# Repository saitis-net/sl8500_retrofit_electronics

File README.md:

# sl8500_retrofit_electronics
Kicad projects for the hardware parts

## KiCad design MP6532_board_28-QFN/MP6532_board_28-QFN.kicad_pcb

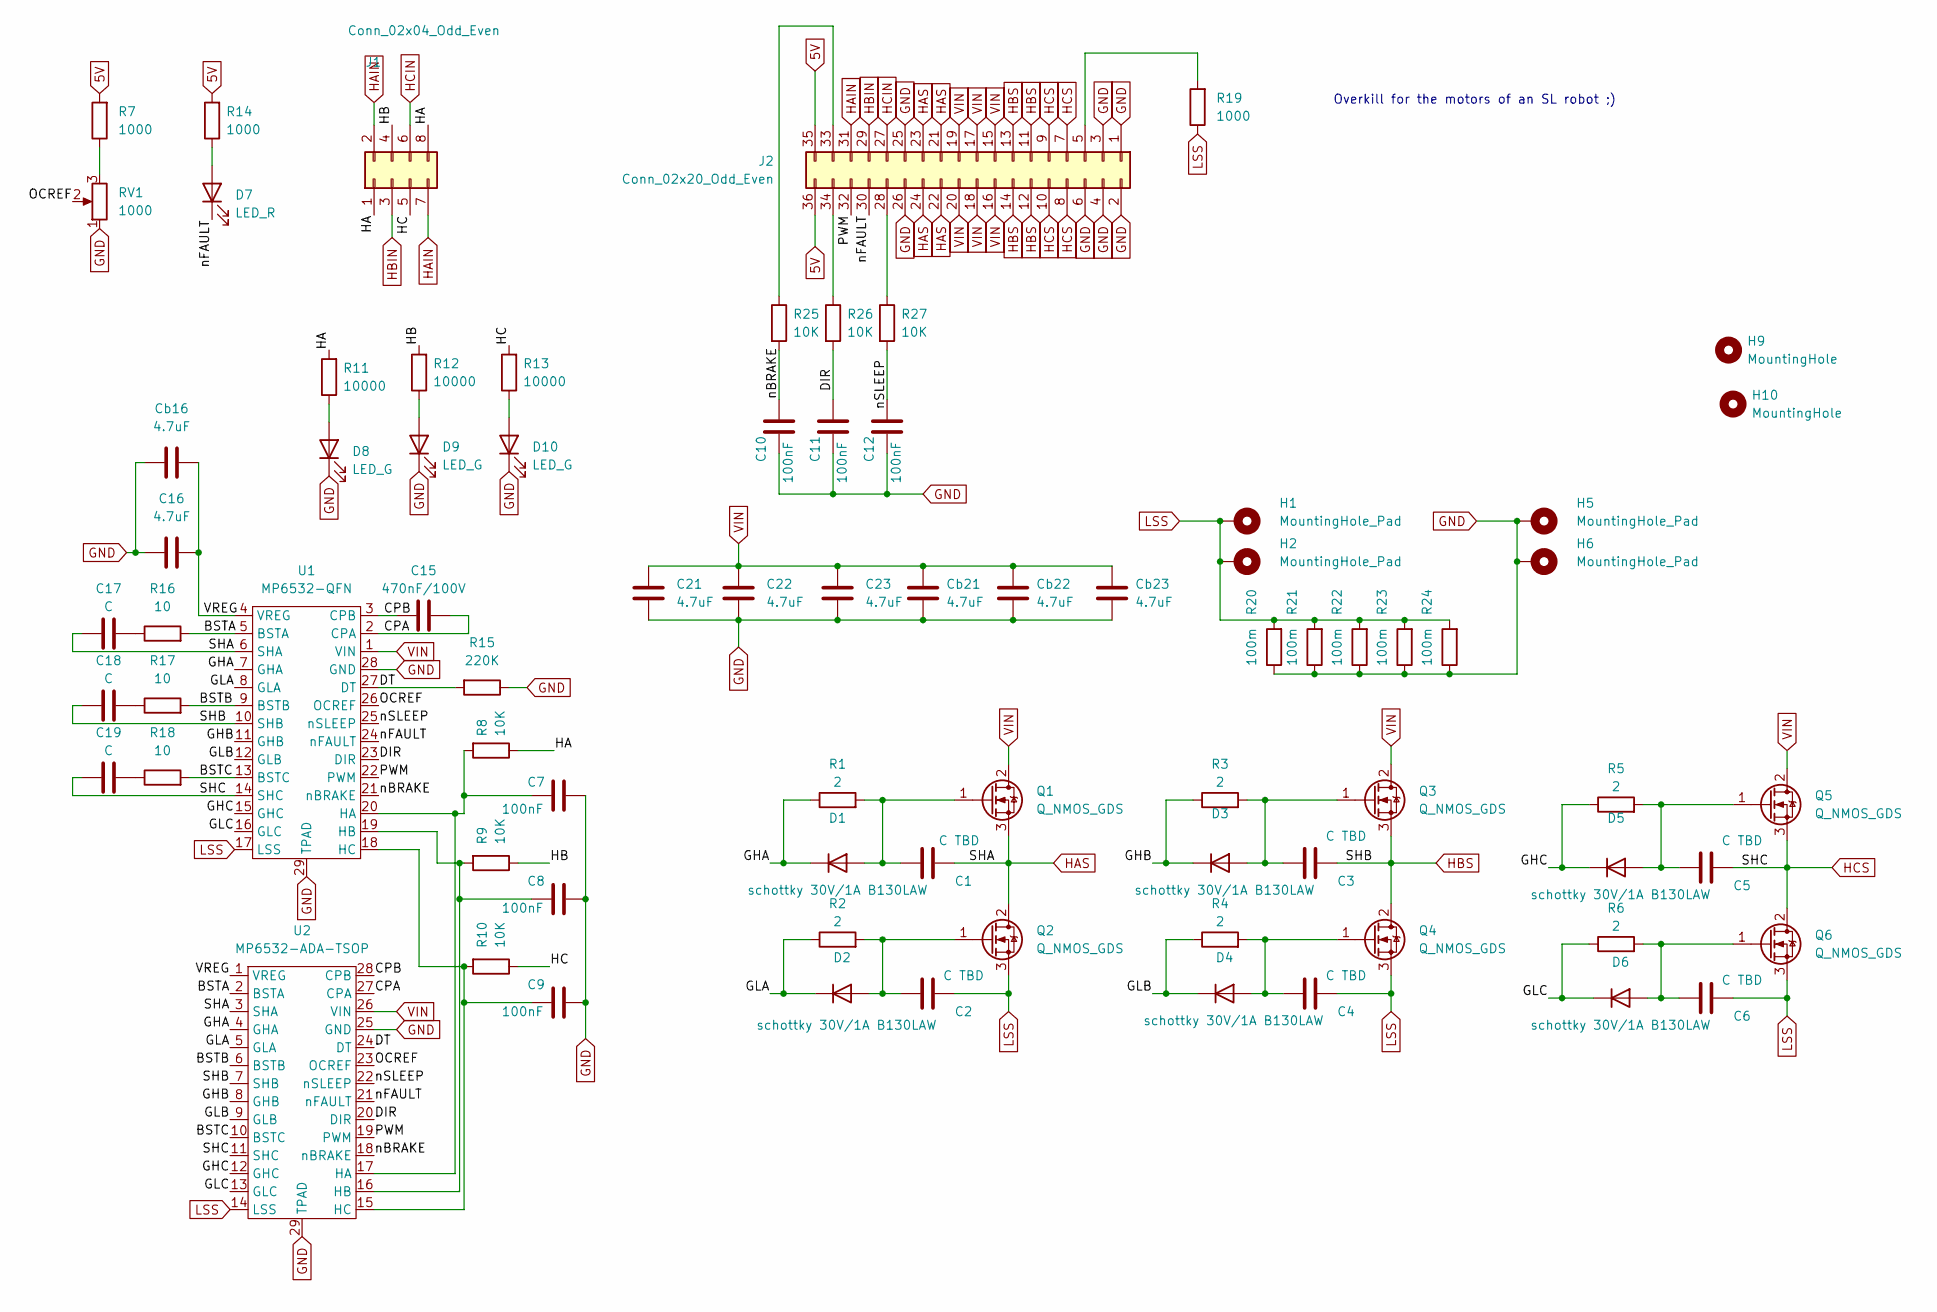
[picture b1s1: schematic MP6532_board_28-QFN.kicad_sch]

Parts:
C1, C2, C3, C4, C5, C6: C TBD; C_0603_1608Metric
C7, C8, C9, C10, C11, C12: 100nF; C_0603_1608Metric
C15: 470nF/100V; C_0805_2012Metric
C16, C21, C22, C23: 4.7uF; C_1210_3225Metric
C17, C18, C19: C; C_0603_1608Metric
Cb16, Cb21, Cb22, Cb23: 4.7uF; C_1210_3225Metric
D1, D2, D3, D4, D5, D6: schottky 30V/1A B130LAW; D_SOD-123
D7: LED_R; LED_0805_2012Metric
D8, D9, D10: LED_G; LED_0805_2012Metric
H1, H2, H5, H6: MountingHole_Pad; Pin_D1.2mm_L10.2mm_W2.9mm_FlatFork
H9, H10: MountingHole; MountingHole_3.2mm_M3_DIN965
J1: Conn_02x04_Odd_Even; PinHeader_2x04_P2.54mm_Horizontal
J2: Conn_02x20_Odd_Even; PinHeader_2x18_P2.54mm_Horizontal
Q1, Q2, Q3, Q4, Q5, Q6: Q_NMOS_GDS; TO-252-2
R1, R2, R3, R4, R5, R6: 2; R_1210_3225Metric
R7, R14, R19: 1000; R_0603_1608Metric
R8, R9, R10, R25, R26, R27: 10K; R_0603_1608Metric
R11, R12, R13: 10000; R_0603_1608Metric
R15: 220K; R_0603_1608Metric
R16, R17, R18: 10; R_0603_1608Metric
R20, R21, R22, R23, R24: 100m; R_1206_3216Metric
RV1: 1000; Potentiometer_Bourns_3296P_Horizontal
U1: MP6532-QFN; QFN-28-1EP_4x4mm_P0.4mm_EP2.6x2.6mm_ThermalVias
U2: MP6532-ADA-TSOP; 28-pin-deca

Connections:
5V: J2.35, J2.36, R7.2, R14.2
/BSTA: R16.2, U1.5 (BSTA), U2.2 (BSTA)
/BSTB: R17.2, U1.9 (BSTB), U2.6 (BSTB)
/BSTC: R18.2, U1.13 (BSTC), U2.10 (BSTC)
/CPA: C15.2, U1.2 (CPA), U2.27 (CPA)
/CPB: C15.1, U1.3 (CPB), U2.28 (CPB)
/DIR: C11.2, R26.2, U1.23 (DIR), U2.20 (DIR)
/DT: R15.2, U1.27 (DT), U2.24 (DT)
/GHA: D1.1 (K), R1.1, U1.7 (GHA), U2.4 (GHA)
/GHB: D3.1 (K), R3.1, U1.11 (GHB), U2.8 (GHB)
/GHC: D5.1 (K), R5.1, U1.15 (GHC), U2.12 (GHC)
/GLA: D2.1 (K), R2.1, U1.8 (GLA), U2.5 (GLA)
/GLB: D4.1 (K), R4.1, U1.12 (GLB), U2.9 (GLB)
/GLC: D6.1 (K), R6.1, U1.16 (GLC), U2.13 (GLC)
/HA: J1.1, J1.8, R8.1, R11.2
/HB: J1.4, R9.1, R12.2
/HC: J1.5, R10.1, R13.2
/OCREF: RV1.2, U1.26 (OCREF), U2.23 (OCREF)
/PWM: J2.32, U1.22 (PWM), U2.19 (PWM)
/VREG: C16.1, Cb16.1, U1.4 (VREG), U2.1 (VREG)
/nBRAKE: C10.2, R25.2, U1.21 (nBRAKE), U2.18 (nBRAKE)
/nFAULT: D7.1 (K), J2.30, U1.24 (nFAULT), U2.21 (nFAULT)
/nSLEEP: C12.2, R27.2, U1.25 (nSLEEP), U2.22 (nSLEEP)
GND: C7.2, C8.2, C9.2, C10.1, C11.1, C12.1, C16.2, C21.2, C22.2, C23.2, Cb16.2, Cb21.2, Cb22.2, Cb23.2, D8.1 (K), D9.1 (K), D10.1 (K), H5.1, H6.1, J2.1, J2.2, J2.3, J2.4, J2.6, J2.25, J2.26, R15.1, R20.1, R21.1, R22.1, R23.1, R24.1, RV1.1, U1.28 (GND), U1.29 (TPAD), U2.25 (GND), U2.29 (TPAD)
HAIN: J1.2, J1.7, J2.31
HAS: C1.1, C17.1, J2.21, J2.22, J2.23, J2.24, Q1.3 (S), Q2.2 (D), U1.6 (SHA), U2.3 (SHA)
HBIN: J1.3, J2.29
HBS: C3.1, C18.1, J2.11, J2.12, J2.13, J2.14, Q3.3 (S), Q4.2 (D), U1.10 (SHB), U2.7 (SHB)
HCIN: J1.6, J2.27
HCS: C5.1, C19.1, J2.7, J2.8, J2.9, J2.10, Q5.3 (S), Q6.2 (D), U1.14 (SHC), U2.11 (SHC)
LSS: C2.1, C4.1, C6.1, H1.1, H2.1, Q2.3 (S), Q4.3 (S), Q6.3 (S), R19.1, R20.2, R21.2, R22.2, R23.2, R24.2, U1.17 (LSS), U2.14 (LSS)
unnamed: C1.2, D1.2 (A), Q1.1 (G), R1.2
unnamed: C2.2, D2.2 (A), Q2.1 (G), R2.2
unnamed: C3.2, D3.2 (A), Q3.1 (G), R3.2
unnamed: C4.2, D4.2 (A), Q4.1 (G), R4.2
unnamed: C5.2, D5.2 (A), Q5.1 (G), R5.2
unnamed: C6.2, D6.2 (A), Q6.1 (G), R6.2
unnamed: C7.1, R8.2, U1.20 (HA), U2.17 (HA)
unnamed: C8.1, R9.2, U1.19 (HB), U2.16 (HB)
unnamed: C9.1, R10.2, U1.18 (HC), U2.15 (HC)
unnamed: C17.2, R16.1
unnamed: C18.2, R17.1
unnamed: C19.2, R18.1
unnamed: D7.2 (A), R14.1
unnamed: D8.2 (A), R11.1
unnamed: D9.2 (A), R12.1
unnamed: D10.2 (A), R13.1
unnamed: J2.5, R19.2
unnamed: J2.28, R27.1
unnamed: J2.33, R25.1
unnamed: J2.34, R26.1
unnamed: R7.1, RV1.3
VIN: C21.1, C22.1, C23.1, Cb21.1, Cb22.1, Cb23.1, J2.15, J2.16, J2.17, J2.18, J2.19, J2.20, Q1.2 (D), Q3.2 (D), Q5.2 (D), U1.1 (VIN), U2.26 (VIN)

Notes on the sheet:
Overkill for the motors of an SL robot ;)

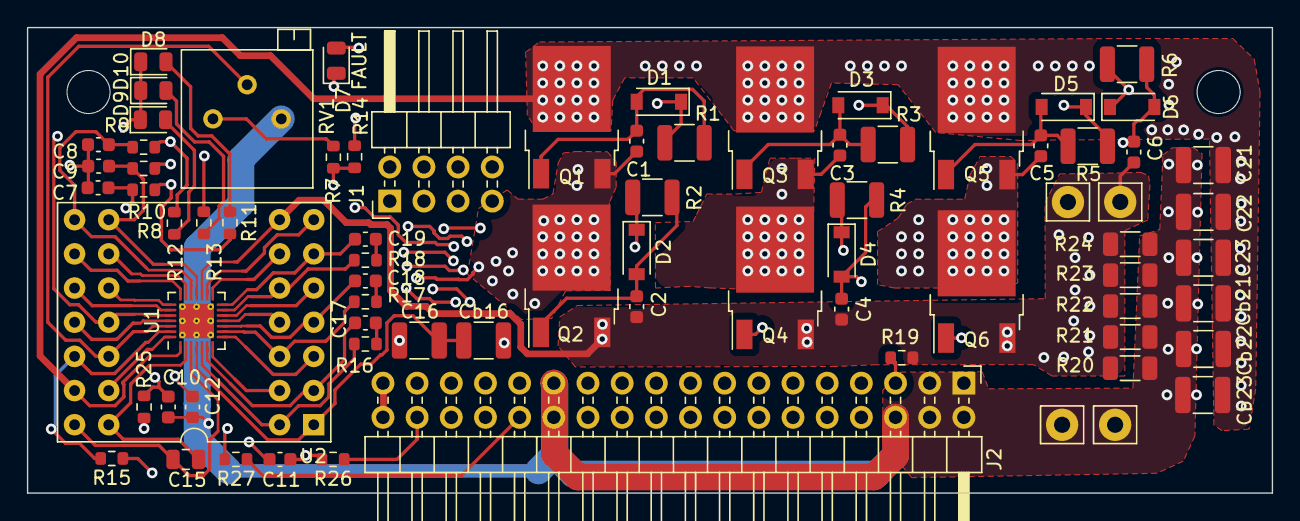
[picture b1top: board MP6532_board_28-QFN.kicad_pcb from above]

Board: 4 copper layers, 92.5 x 34.6 mm, 78 parts (0 on the bottom side), 53 nets.

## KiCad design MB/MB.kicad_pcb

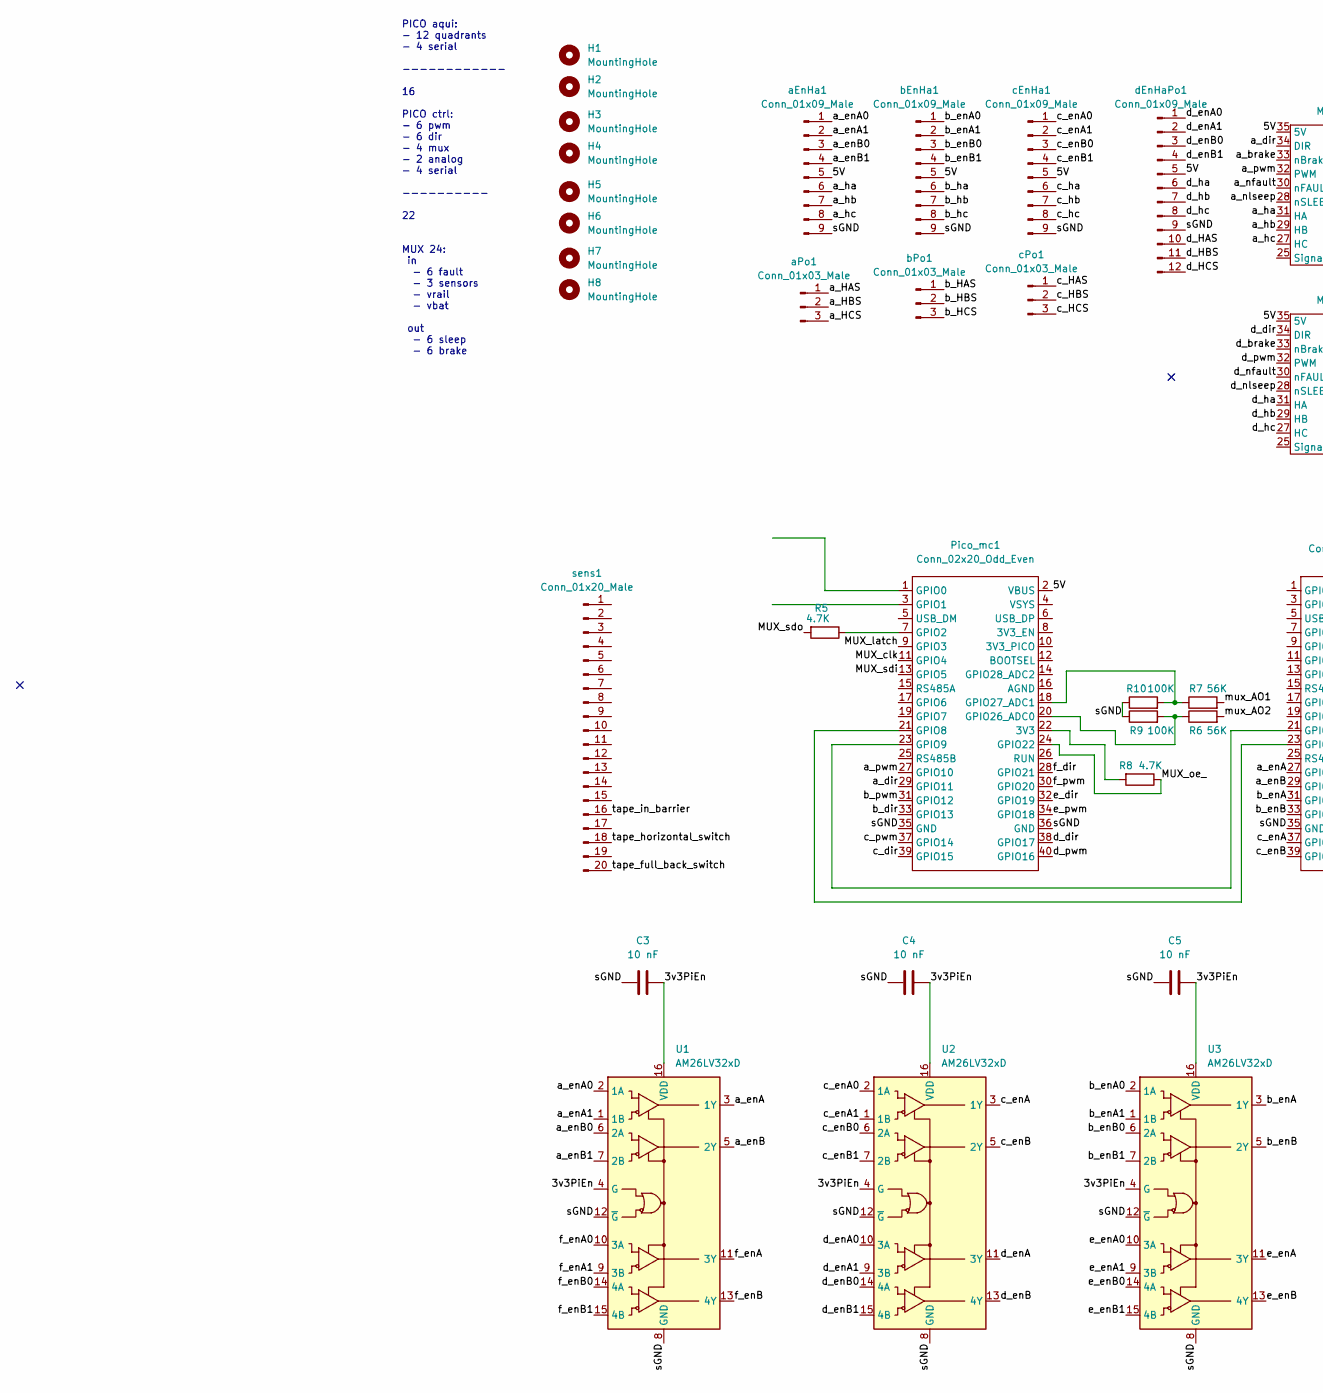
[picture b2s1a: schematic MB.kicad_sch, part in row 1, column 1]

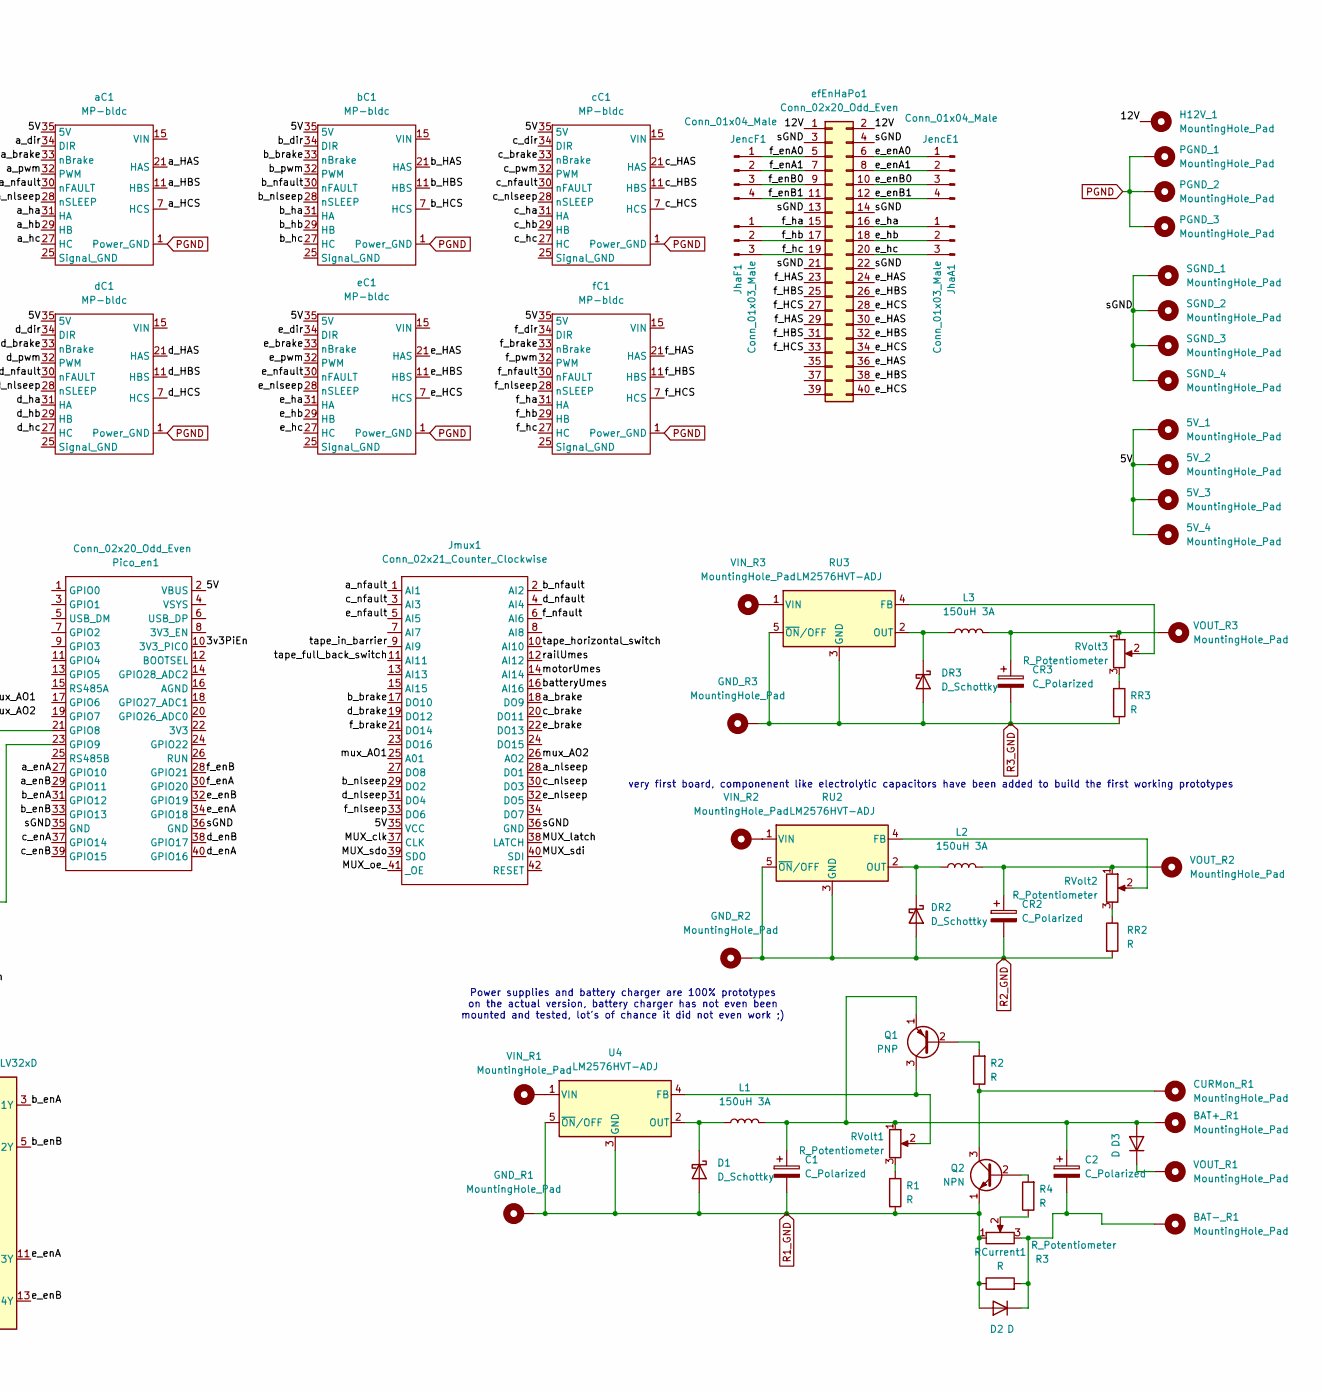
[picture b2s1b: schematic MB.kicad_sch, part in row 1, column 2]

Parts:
5V_1, 5V_2, 5V_3, 5V_4: MountingHole_Pad; Pin_D1.2mm_L10.2mm_W2.9mm_FlatFork
BAT+_R1: MountingHole_Pad; Pin_D1.2mm_L10.2mm_W2.9mm_FlatFork
BAT-_R1: MountingHole_Pad; Pin_D1.2mm_L10.2mm_W2.9mm_FlatFork
C1, C2: C_Polarized; CP_Radial_D12.5mm_P5.00mm
C3, C4, C5: 10 nF; C_Disc_D5.0mm_W2.5mm_P5.00mm
CR2, CR3: C_Polarized; CP_Radial_D12.5mm_P5.00mm
CURMon_R1: MountingHole_Pad; Pin_D1.2mm_L10.2mm_W2.9mm_FlatFork
D1: D_Schottky; D_DO-201AD_P3.81mm_Vertical_AnodeUp
D2, D3: D; D_DO-201AD_P3.81mm_Vertical_AnodeUp
DR2, DR3: D_Schottky; D_DO-201AD_P3.81mm_Vertical_AnodeUp
GND_R1, GND_R2, GND_R3: MountingHole_Pad; Pin_D1.2mm_L10.2mm_W2.9mm_FlatFork
H1, H2, H3, H4, H5, H6, H7, H8: MountingHole; MountingHole_4.5mm
H12V_1: MountingHole_Pad; Pin_D1.2mm_L10.2mm_W2.9mm_FlatFork
JencE1: Conn_01x04_Male; PinHeader_1x04_P2.54mm_Vertical
JencF1: Conn_01x04_Male; PinHeader_1x04_P2.54mm_Vertical
JhaA1: Conn_01x03_Male; PinHeader_1x03_P2.54mm_Vertical
JhaF1: Conn_01x03_Male; PinHeader_1x03_P2.54mm_Vertical
Jmux1: Conn_02x21_Counter_Clockwise; PinSocket_2x21_P2.54mm_Vertical
L1, L2, L3: 150uH 3A; L_Toroid_Vertical_L24.6mm_W15.5mm_P11.44mm_Pulse_KM-4
PGND_1, PGND_2, PGND_3: MountingHole_Pad; Pin_D1.2mm_L10.2mm_W2.9mm_FlatFork
Pico_en1: Conn_02x20_Odd_Even; PinSocket_2x20_P2.54mm_Vertical
Pico_mc1: Conn_02x20_Odd_Even; PinSocket_2x20_P2.54mm_Vertical
Q1: PNP; TO-92L_Wide
Q2: NPN; TO-92L_Wide
R1, R2, R4: R; R_Axial_DIN0207_L6.3mm_D2.5mm_P2.54mm_Vertical
R3: R; D_DO-201AD_P3.81mm_Vertical_AnodeUp
R5, R8: 4.7K; R_Axial_DIN0207_L6.3mm_D2.5mm_P2.54mm_Vertical
R6, R7: 56K; R_Axial_DIN0207_L6.3mm_D2.5mm_P2.54mm_Vertical
R9, R10: 100K; R_Axial_DIN0207_L6.3mm_D2.5mm_P2.54mm_Vertical
RCurrent1: R_Potentiometer; Potentiometer_Bourns_3296P_Horizontal
RR2, RR3: R; R_Axial_DIN0207_L6.3mm_D2.5mm_P2.54mm_Vertical
RU2, RU3: LM2576HVT-ADJ; TO-220-5_P3.4x3.7mm_StaggerEven_Lead3.8mm_Vertical
RVolt1, RVolt2, RVolt3: R_Potentiometer; Potentiometer_Bourns_3296P_Horizontal
SGND_1, SGND_2, SGND_3, SGND_4: MountingHole_Pad; Pin_D1.2mm_L10.2mm_W2.9mm_FlatFork
U1, U2, U3: AM26LV32xD; SOIC-16_3.9x9.9mm_P1.27mm
U4: LM2576HVT-ADJ; TO-220-5_P3.4x3.7mm_StaggerEven_Lead3.8mm_Vertical
VIN_R1, VIN_R2, VIN_R3: MountingHole_Pad; Pin_D1.2mm_L10.2mm_W2.9mm_FlatFork
VOUT_R1, VOUT_R2, VOUT_R3: MountingHole_Pad; Pin_D1.2mm_L10.2mm_W2.9mm_FlatFork
aC1: MP-bldc; MP-bldc-module
aEnHa1: Conn_01x09_Male; PinHeader_1x09_P2.54mm_Vertical
aPo1: Conn_01x03_Male; CONN_SD-41771-001_M450_03_MOL
bC1: MP-bldc; MP-bldc-module
bEnHa1: Conn_01x09_Male; PinHeader_1x09_P2.54mm_Vertical
bPo1: Conn_01x03_Male; CONN_SD-41771-001_M450_03_MOL
cC1: MP-bldc; MP-bldc-module
cEnHa1: Conn_01x09_Male; PinHeader_1x09_P2.54mm_Vertical
cPo1: Conn_01x03_Male; CONN_SD-41771-001_M450_03_MOL
dC1: MP-bldc; MP-bldc-module
dEnHaPo1: Conn_01x09_Male; PinHeader_1x12_P2.54mm_Vertical
eC1: MP-bldc; MP-bldc-module
efEnHaPo1: Conn_02x20_Odd_Even; PinHeader_2x20_P1.27mm_Vertical
fC1: MP-bldc; MP-bldc-module
sens1: Conn_01x20_Male; PinHeader_1x20_P1.27mm_Vertical

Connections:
/3v3PiEn: C3.2, C4.2, C5.2, Pico_en1.10 (3V3_PICO), U1.4 (G), U1.16 (VDD), U2.4 (G), U2.16 (VDD), U3.4 (G), U3.16 (VDD)
/5V: 5V_1.1, 5V_2.1, 5V_3.1, 5V_4.1, Jmux1.35 (VCC), Pico_en1.2 (VBUS), Pico_mc1.2 (VBUS), aC1.35 (5V), aEnHa1.5, bC1.35 (5V), bEnHa1.5, cC1.35 (5V), cEnHa1.5, dC1.35 (5V), dEnHaPo1.5, eC1.35 (5V), fC1.35 (5V)
/12V: H12V_1.1, efEnHaPo1.1, efEnHaPo1.2
/MUX_clk: Jmux1.37 (CLK), Pico_mc1.11 (GPIO4)
/MUX_latch: Jmux1.38 (LATCH), Pico_mc1.9 (GPIO3)
/MUX_oe_: Jmux1.41 (_OE), Pico_mc1.24 (GPIO22), R8.1
/MUX_sdi: Jmux1.40 (SDI), Pico_mc1.13 (GPIO5)
/MUX_sdo: Jmux1.39 (SDO), R5.2
/a_HAS: aC1.21 (HAS), aPo1.1
/a_HBS: aC1.11 (HBS), aPo1.2
/a_HCS: aC1.7 (HCS), aPo1.3
/a_brake: Jmux1.18 (DO9), aC1.33 (nBrake)
/a_dir: Pico_mc1.29 (GPIO11), aC1.34 (DIR)
/a_enA: Pico_en1.27 (GPIO10), U1.3 (1Y)
/a_enA0: U1.2 (1A), aEnHa1.1
/a_enA1: U1.1 (1B), aEnHa1.2
/a_enB: Pico_en1.29 (GPIO11), U1.5 (2Y)
/a_enB0: U1.6 (2A), aEnHa1.3
/a_enB1: U1.7 (2B), aEnHa1.4
/a_ha: aC1.31 (HA), aEnHa1.6
/a_hb: aC1.29 (HB), aEnHa1.7
/a_hc: aC1.27 (HC), aEnHa1.8
/a_nfault: Jmux1.1 (AI1), aC1.30 (nFAULT)
/a_nlseep: Jmux1.28 (DO1), aC1.28 (nSLEEP)
/a_pwm: Pico_mc1.27 (GPIO10), aC1.32 (PWM)
/b_HAS: bC1.21 (HAS), bPo1.1
/b_HBS: bC1.11 (HBS), bPo1.2
/b_HCS: bC1.7 (HCS), bPo1.3
/b_brake: Jmux1.17 (DO10), bC1.33 (nBrake)
/b_dir: Pico_mc1.33 (GPIO13), bC1.34 (DIR)
/b_enA: Pico_en1.31 (GPIO12), U3.3 (1Y)
/b_enA0: U3.2 (1A), bEnHa1.1
/b_enA1: U3.1 (1B), bEnHa1.2
/b_enB: Pico_en1.33 (GPIO13), U3.5 (2Y)
/b_enB0: U3.6 (2A), bEnHa1.3
/b_enB1: U3.7 (2B), bEnHa1.4
/b_ha: bC1.31 (HA), bEnHa1.6
/b_hb: bC1.29 (HB), bEnHa1.7
/b_hc: bC1.27 (HC), bEnHa1.8
/b_nfault: Jmux1.2 (AI2), bC1.30 (nFAULT)
/b_nlseep: Jmux1.29 (DO2), bC1.28 (nSLEEP)
/b_pwm: Pico_mc1.31 (GPIO12), bC1.32 (PWM)
/batteryUmes: Jmux1.16 (AI16)
/c_HAS: cC1.21 (HAS), cPo1.1
/c_HBS: cC1.11 (HBS), cPo1.2
/c_HCS: cC1.7 (HCS), cPo1.3
/c_brake: Jmux1.20 (DO11), cC1.33 (nBrake)
/c_dir: Pico_mc1.39 (GPIO15), cC1.34 (DIR)
/c_enA: Pico_en1.37 (GPIO14), U2.3 (1Y)
/c_enA0: U2.2 (1A), cEnHa1.1
/c_enA1: U2.1 (1B), cEnHa1.2
/c_enB: Pico_en1.39 (GPIO15), U2.5 (2Y)
/c_enB0: U2.6 (2A), cEnHa1.3
/c_enB1: U2.7 (2B), cEnHa1.4
/c_ha: cC1.31 (HA), cEnHa1.6
/c_hb: cC1.29 (HB), cEnHa1.7
/c_hc: cC1.27 (HC), cEnHa1.8
/c_nfault: Jmux1.3 (AI3), cC1.30 (nFAULT)
/c_nlseep: Jmux1.30 (DO3), cC1.28 (nSLEEP)
/c_pwm: Pico_mc1.37 (GPIO14), cC1.32 (PWM)
/d_HAS: dC1.21 (HAS), dEnHaPo1.10
/d_HBS: dC1.11 (HBS), dEnHaPo1.11
/d_HCS: dC1.7 (HCS), dEnHaPo1.12
/d_brake: Jmux1.19 (DO12), dC1.33 (nBrake)
/d_dir: Pico_mc1.38 (GPIO17), dC1.34 (DIR)
/d_enA: Pico_en1.40 (GPIO16), U2.11 (3Y)
/d_enA0: U2.10 (3A), dEnHaPo1.1
/d_enA1: U2.9 (3B), dEnHaPo1.2
/d_enB: Pico_en1.38 (GPIO17), U2.13 (4Y)
/d_enB0: U2.14 (4A), dEnHaPo1.3
/d_enB1: U2.15 (4B), dEnHaPo1.4
/d_ha: dC1.31 (HA), dEnHaPo1.6
/d_hb: dC1.29 (HB), dEnHaPo1.7
/d_hc: dC1.27 (HC), dEnHaPo1.8
/d_nfault: Jmux1.4 (AI4), dC1.30 (nFAULT)
/d_nlseep: Jmux1.31 (DO4), dC1.28 (nSLEEP)
/d_pwm: Pico_mc1.40 (GPIO16), dC1.32 (PWM)
/e_HAS: eC1.21 (HAS), efEnHaPo1.24, efEnHaPo1.30, efEnHaPo1.36
/e_HBS: eC1.11 (HBS), efEnHaPo1.26, efEnHaPo1.32, efEnHaPo1.38
/e_HCS: eC1.7 (HCS), efEnHaPo1.28, efEnHaPo1.34, efEnHaPo1.40
/e_brake: Jmux1.22 (DO13), eC1.33 (nBrake)
/e_dir: Pico_mc1.32 (GPIO19), eC1.34 (DIR)
/e_enA: Pico_en1.34 (GPIO18), U3.11 (3Y)
/e_enA0: JencE1.1, U3.10 (3A), efEnHaPo1.6
/e_enA1: JencE1.2, U3.9 (3B), efEnHaPo1.8
/e_enB: Pico_en1.32 (GPIO19), U3.13 (4Y)
/e_enB0: JencE1.3, U3.14 (4A), efEnHaPo1.10
/e_enB1: JencE1.4, U3.15 (4B), efEnHaPo1.12
/e_ha: JhaA1.1, eC1.31 (HA), efEnHaPo1.16
/e_hb: JhaA1.2, eC1.29 (HB), efEnHaPo1.18
/e_hc: JhaA1.3, eC1.27 (HC), efEnHaPo1.20
/e_nfault: Jmux1.5 (AI5), eC1.30 (nFAULT)
/e_nlseep: Jmux1.32 (DO5), eC1.28 (nSLEEP)
/e_pwm: Pico_mc1.34 (GPIO18), eC1.32 (PWM)
/f_HAS: efEnHaPo1.23, efEnHaPo1.29, fC1.21 (HAS)
/f_HBS: efEnHaPo1.25, efEnHaPo1.31, fC1.11 (HBS)
/f_HCS: efEnHaPo1.27, efEnHaPo1.33, fC1.7 (HCS)
/f_brake: Jmux1.21 (DO14), fC1.33 (nBrake)
/f_dir: Pico_mc1.28 (GPIO21), fC1.34 (DIR)
/f_enA: Pico_en1.30 (GPIO20), U1.11 (3Y)
/f_enA0: JencF1.1, U1.10 (3A), efEnHaPo1.5
/f_enA1: JencF1.2, U1.9 (3B), efEnHaPo1.7
/f_enB: Pico_en1.28 (GPIO21), U1.13 (4Y)
/f_enB0: JencF1.3, U1.14 (4A), efEnHaPo1.9
/f_enB1: JencF1.4, U1.15 (4B), efEnHaPo1.11
/f_ha: JhaF1.1, efEnHaPo1.15, fC1.31 (HA)
/f_hb: JhaF1.2, efEnHaPo1.17, fC1.29 (HB)
/f_hc: JhaF1.3, efEnHaPo1.19, fC1.27 (HC)
/f_nfault: Jmux1.6 (AI6), fC1.30 (nFAULT)
/f_nlseep: Jmux1.33 (DO6), fC1.28 (nSLEEP)
/f_pwm: Pico_mc1.30 (GPIO20), fC1.32 (PWM)
/motorUmes: Jmux1.14 (AI14)
/mux_AO1: Jmux1.25 (A01), R7.2
/mux_AO2: Jmux1.26 (AO2), R6.2
/railUmes: Jmux1.12 (AI12)
/sGND: C3.1, C4.1, C5.1, Jmux1.36 (GND), Pico_en1.35 (GND), Pico_en1.36 (GND), Pico_mc1.35 (GND), Pico_mc1.36 (GND), R9.1, R10.1, SGND_1.1, SGND_2.1, SGND_3.1, SGND_4.1, U1.8 (GND), U1.12 (~G), U2.8 (GND), U2.12 (~G), U3.8 (GND), U3.12 (~G), aEnHa1.9, bEnHa1.9, cEnHa1.9, dEnHaPo1.9, efEnHaPo1.3, efEnHaPo1.4, efEnHaPo1.13, efEnHaPo1.14, efEnHaPo1.21, efEnHaPo1.22
/tape_full_back_switch: Jmux1.11 (AI11), sens1.20
/tape_horizontal_switch: Jmux1.10 (AI10), sens1.18
/tape_in_barrier: Jmux1.9 (AI9), sens1.16
unnamed: BAT+_R1.1, C1.1, C2.1, D3.2 (A), L1.2, Q1.1 (E), RVolt1.1
unnamed: BAT-_R1.1, C2.2, D2.1 (K), R3.2, RCurrent1.3
unnamed: CR2.1, L2.2, RVolt2.1, VOUT_R2.1
unnamed: CR3.1, L3.2, RVolt3.1, VOUT_R3.1
unnamed: CURMon_R1.1, Q2.3 (C), R2.1
unnamed: D1.1 (K), L1.1, U4.2 (OUT)
unnamed: D3.1 (K), VOUT_R1.1
unnamed: DR2.1 (K), L2.1, RU2.2 (OUT)
unnamed: DR3.1 (K), L3.1, RU3.2 (OUT)
unnamed: Pico_en1.21 (GPIO8), Pico_mc1.23 (GPIO9)
unnamed: Pico_en1.23 (GPIO9), Pico_mc1.21 (GPIO8)
unnamed: Pico_mc1.7 (GPIO2), R5.1
unnamed: Pico_mc1.18 (GPIO27_ADC1), R7.1, R10.2
unnamed: Pico_mc1.20 (GPIO26_ADC0), R6.1, R9.2
unnamed: Pico_mc1.22 (3V3), R8.2
unnamed: Q1.2 (B), R2.2
unnamed: Q1.3 (C), RVolt1.2, U4.4 (FB)
unnamed: Q2.2 (B), R4.2
unnamed: R1.1, RVolt1.3
unnamed: R4.1, RCurrent1.2
unnamed: RR2.1, RVolt2.3
unnamed: RR3.1, RVolt3.3
unnamed: RU2.1 (VIN), VIN_R2.1
unnamed: RU2.4 (FB), RVolt2.2
unnamed: RU3.1 (VIN), VIN_R3.1
unnamed: RU3.4 (FB), RVolt3.2
unnamed: U4.1 (VIN), VIN_R1.1
PGND: PGND_1.1, PGND_2.1, PGND_3.1, aC1.1 (Power_GND), bC1.1 (Power_GND), cC1.1 (Power_GND), dC1.1 (Power_GND), eC1.1 (Power_GND), fC1.1 (Power_GND)
R1_GND: C1.2, D1.2 (A), D2.2 (A), GND_R1.1, Q2.1 (E), R1.2, R3.1, RCurrent1.1, U4.3 (GND), U4.5 (~ON/OFF)
R2_GND: CR2.2, DR2.2 (A), GND_R2.1, RR2.2, RU2.3 (GND), RU2.5 (~ON/OFF)
R3_GND: CR3.2, DR3.2 (A), GND_R3.1, RR3.2, RU3.3 (GND), RU3.5 (~ON/OFF)

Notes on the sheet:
Power supplies and battery charger are 100% prototypes on the actual version, battery charger has not even been mounted and tested, lot's of chance it did not even work ;)
very first board, componenent like electrolytic capacitors have been added to build the first working prototypes
PICO aqui: - 12 quadrants - 4 serial ------------ 16 PICO ctrl: - 6 pwm - 6 dir - 4 mux - 2 analog - 4 serial ---------- 22 MUX 24: in - 6 fault - 3 sensors - vrail - vbat out - 6 sleep - 6 brake

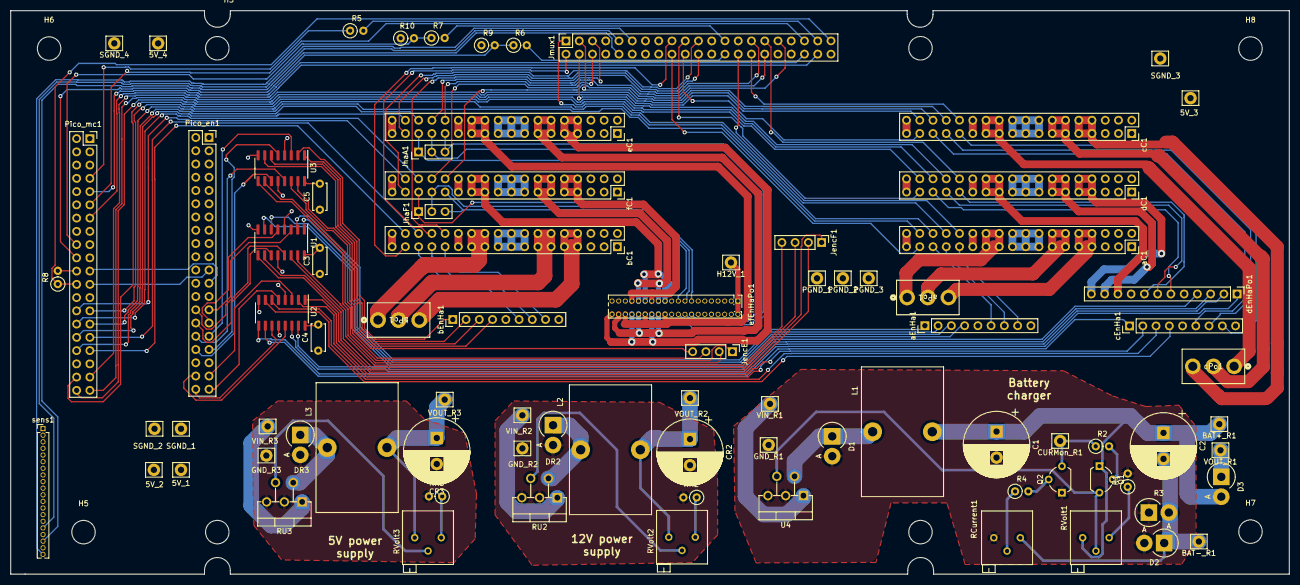
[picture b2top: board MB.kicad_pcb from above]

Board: 4 copper layers, 245.1 x 108.0 mm, 93 parts (0 on the bottom side), 147 nets.

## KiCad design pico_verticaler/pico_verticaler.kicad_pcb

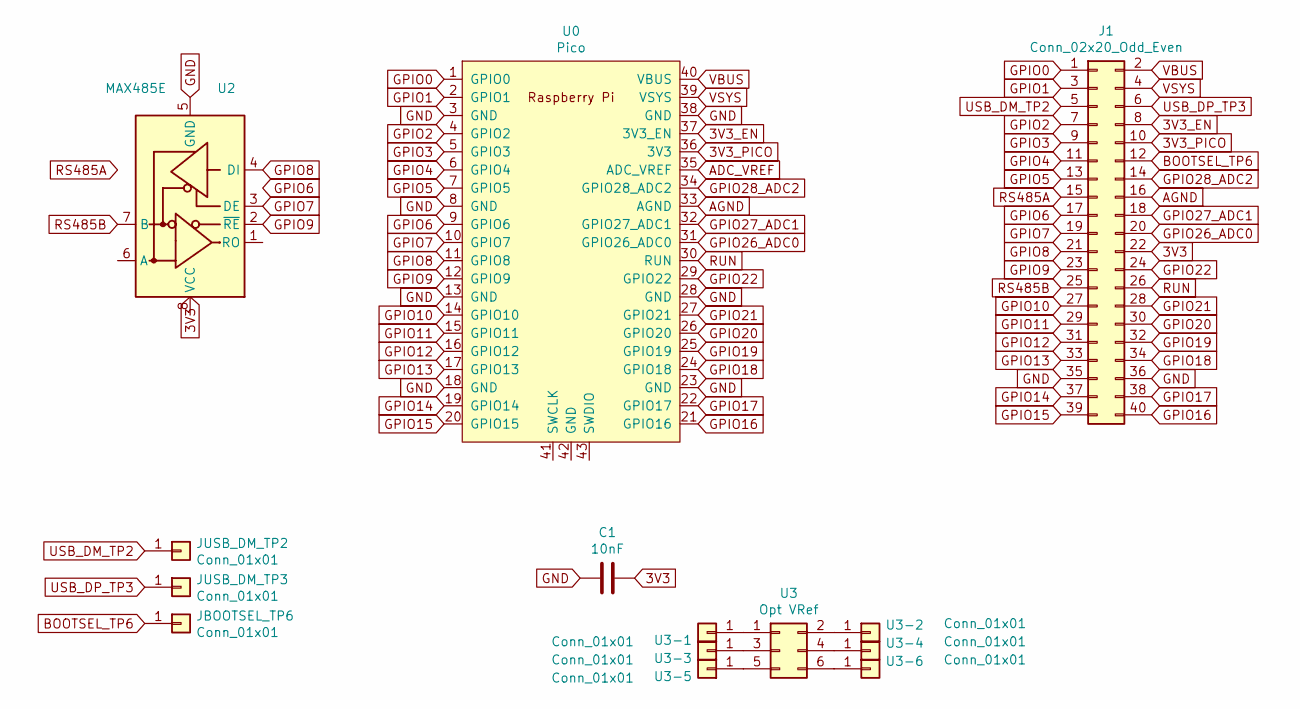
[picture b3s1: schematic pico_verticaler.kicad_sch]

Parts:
C1: 10nF; C_1206_3216Metric
J1: Conn_02x20_Odd_Even; PinHeader_2x20_P2.54mm_Vertical
JBOOTSEL_TP6: Conn_01x01; panani
JUSB_DM_TP2, JUSB_DM_TP3: Conn_01x01; panani
U0: Pico; RPi_Pico_SMD_TH
U2: MAX485E; SOIC-8_3.9x4.9mm_P1.27mm
U3: Opt VRef; SOT-23-6
U3-1, U3-2, U3-3, U3-4, U3-5, U3-6: Conn_01x01; TestPoint_Pad_1.5x1.5mm

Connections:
3V3: C1.1, J1.22, U2.8 (VCC)
3V3_EN: J1.8, U0.37 (3V3_EN)
3V3_PICO: J1.10, U0.36 (3V3)
ADC_VREF: U0.35 (ADC_VREF)
AGND: J1.16, U0.33 (AGND)
BOOTSEL_TP6: J1.12, JBOOTSEL_TP6.1
GND: C1.2, J1.35, J1.36, U0.3 (GND), U0.8 (GND), U0.13 (GND), U0.18 (GND), U0.23 (GND), U0.28 (GND), U0.38 (GND), U2.5 (GND)
GPIO0: J1.1, U0.1 (GPIO0)
GPIO1: J1.3, U0.2 (GPIO1)
GPIO2: J1.7, U0.4 (GPIO2)
GPIO3: J1.9, U0.5 (GPIO3)
GPIO4: J1.11, U0.6 (GPIO4)
GPIO5: J1.13, U0.7 (GPIO5)
GPIO8: J1.21, U0.11 (GPIO8), U2.4 (DI)
GPIO10: J1.27, U0.14 (GPIO10)
GPIO11: J1.29, U0.15 (GPIO11)
GPIO12: J1.31, U0.16 (GPIO12)
GPIO13: J1.33, U0.17 (GPIO13)
GPIO14: J1.37, U0.19 (GPIO14)
GPIO15: J1.39, U0.20 (GPIO15)
GPIO16: J1.40, U0.21 (GPIO16)
GPIO17: J1.38, U0.22 (GPIO17)
GPIO18: J1.34, U0.24 (GPIO18)
GPIO19: J1.32, U0.25 (GPIO19)
GPIO20: J1.30, U0.26 (GPIO20)
GPIO21: J1.28, U0.27 (GPIO21)
GPIO22: J1.24, U0.29 (GPIO22)
GPIO26_ADC0: J1.20, U0.31 (GPIO26_ADC0)
GPIO27_ADC1: J1.18, U0.32 (GPIO27_ADC1)
GPIO28_ADC2: J1.14, U0.34 (GPIO28_ADC2)
unnamed: U3.1, U3-1.1
unnamed: U3.2, U3-2.1
unnamed: U3.3, U3-3.1
unnamed: U3.4, U3-4.1
unnamed: U3.5, U3-5.1
unnamed: U3.6, U3-6.1
RS485A: J1.15, U2.6 (A)
RS485B: J1.25, U2.7 (B)
RUN: J1.26, U0.30 (RUN)
USB_DM_TP2: J1.5, JUSB_DM_TP2.1
USB_DP_TP3: J1.6, JUSB_DM_TP3.1
VBUS: J1.2, U0.40 (VBUS)
VSYS: J1.4, U0.39 (VSYS)

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
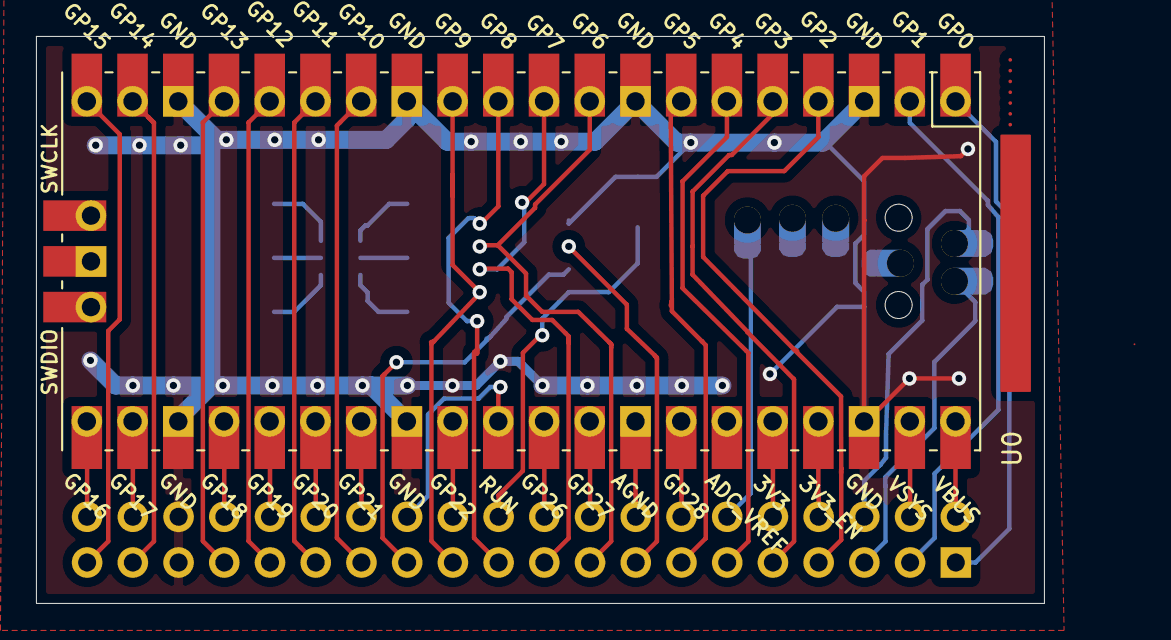
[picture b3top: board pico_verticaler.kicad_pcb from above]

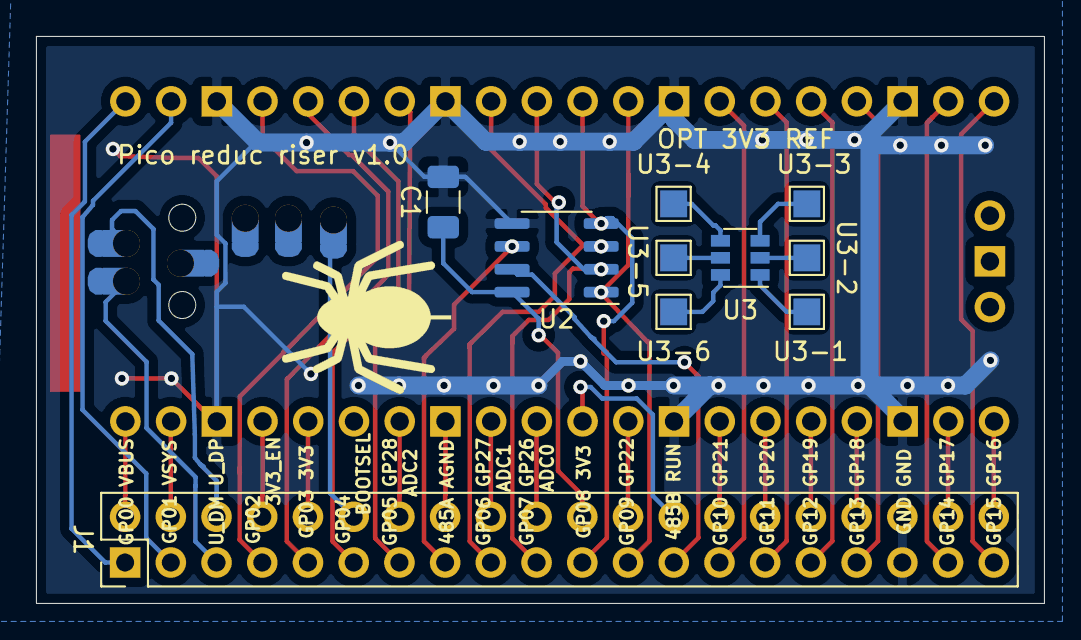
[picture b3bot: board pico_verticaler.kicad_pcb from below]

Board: 2 copper layers, 56.0 x 31.5 mm, 14 parts (13 on the bottom side), 45 nets.

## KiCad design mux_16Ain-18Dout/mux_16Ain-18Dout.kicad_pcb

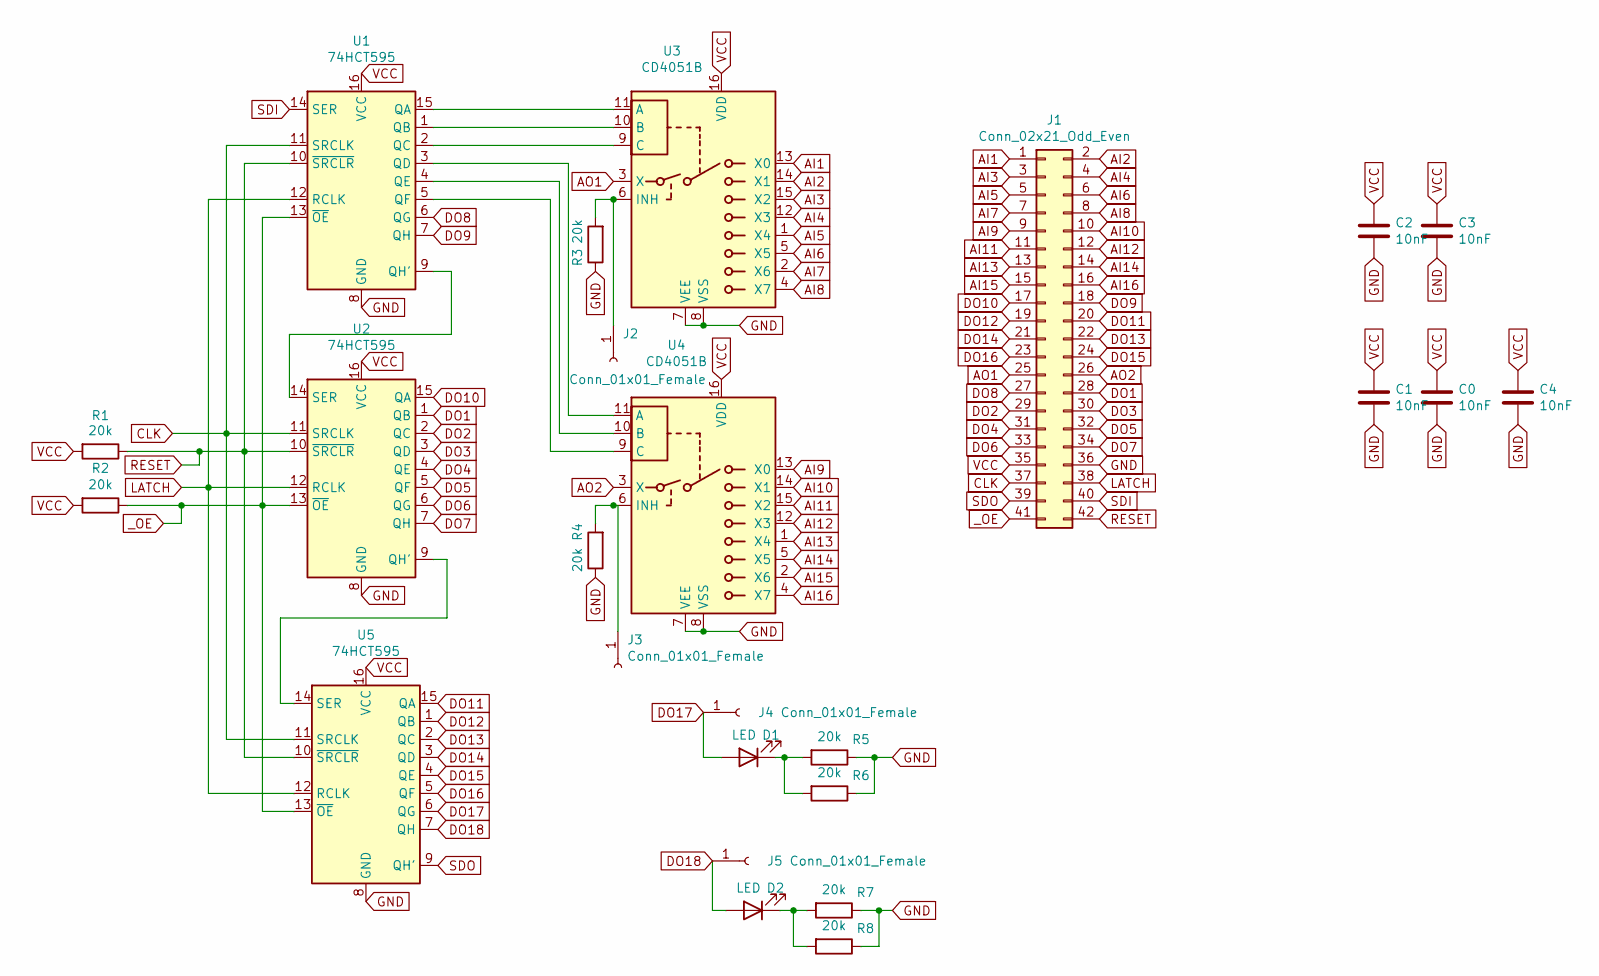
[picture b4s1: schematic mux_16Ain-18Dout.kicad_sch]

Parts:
C0, C1, C2, C3, C4: 10nF; C_1206_3216Metric; LCSC Part C107204
D1, D2: LED; D_0805_2012Metric
J1: Conn_02x21_Odd_Even; PinHeader_2x21_P2.54mm_Vertical; JLCPCB BOM 0
J2, J3, J4, J5: Conn_01x01_Female; Pin_D0.9mm_L10.0mm_W2.4mm_FlatFork; JLCPCB BOM 0
R1, R2, R3, R4, R5, R6, R7, R8: 20k; R_0603_1608Metric; LCSC Part C4184
U1, U2, U5: 74HCT595; SOIC-16_3.9x9.9mm_P1.27mm; LCSC Part C282339
U3, U4: CD4051B; SOP-16_4.55x10.3mm_P1.27mm; LCSC Part C507163

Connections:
AI1: J1.1, U3.13 (X0)
AI2: J1.2, U3.14 (X1)
AI3: J1.3, U3.15 (X2)
AI4: J1.4, U3.12 (X3)
AI5: J1.5, U3.1 (X4)
AI6: J1.6, U3.5 (X5)
AI7: J1.7, U3.2 (X6)
AI8: J1.8, U3.4 (X7)
AI9: J1.9, U4.13 (X0)
AI10: J1.10, U4.14 (X1)
AI11: J1.11, U4.15 (X2)
AI12: J1.12, U4.12 (X3)
AI13: J1.13, U4.1 (X4)
AI14: J1.14, U4.5 (X5)
AI15: J1.15, U4.2 (X6)
AI16: J1.16, U4.4 (X7)
AO1: J1.25, U3.3 (X)
AO2: J1.26, U4.3 (X)
CLK: J1.37, U1.11 (SRCLK), U2.11 (SRCLK), U5.11 (SRCLK)
DO1: J1.28, U2.1 (QB)
DO2: J1.29, U2.2 (QC)
DO3: J1.30, U2.3 (QD)
DO4: J1.31, U2.4 (QE)
DO5: J1.32, U2.5 (QF)
DO6: J1.33, U2.6 (QG)
DO7: J1.34, U2.7 (QH)
DO8: J1.27, U1.6 (QG)
DO9: J1.18, U1.7 (QH)
DO10: J1.17, U2.15 (QA)
DO11: J1.20, U5.15 (QA)
DO12: J1.19, U5.1 (QB)
DO13: J1.22, U5.2 (QC)
DO14: J1.21, U5.3 (QD)
DO15: J1.24, U5.4 (QE)
DO16: J1.23, U5.5 (QF)
DO17: D1.2 (A), J4.1, U5.6 (QG)
DO18: D2.2 (A), J5.1, U5.7 (QH)
GND: C0.2, C1.2, C2.2, C3.2, C4.2, J1.36, R3.1, R4.1, R5.1, R6.1, R7.1, R8.1, U1.8 (GND), U2.8 (GND), U3.7 (VEE), U3.8 (VSS), U4.7 (VEE), U4.8 (VSS), U5.8 (GND)
LATCH: J1.38, U1.12 (RCLK), U2.12 (RCLK), U5.12 (RCLK)
unnamed: D1.1 (K), R5.2, R6.2
unnamed: D2.1 (K), R7.2, R8.2
unnamed: J2.1, R3.2, U3.6 (INH)
unnamed: J3.1, R4.2, U4.6 (INH)
unnamed: U1.1 (QB), U3.10 (B)
unnamed: U1.2 (QC), U3.9 (C)
unnamed: U1.3 (QD), U4.11 (A)
unnamed: U1.4 (QE), U4.10 (B)
unnamed: U1.5 (QF), U4.9 (C)
unnamed: U1.9 (QH'), U2.14 (SER)
unnamed: U1.15 (QA), U3.11 (A)
unnamed: U2.9 (QH'), U5.14 (SER)
RESET: J1.42, R1.1, U1.10 (~SRCLR), U2.10 (~SRCLR), U5.10 (~SRCLR)
SDI: J1.40, U1.14 (SER)
SDO: J1.39, U5.9 (QH')
VCC: C0.1, C1.1, C2.1, C3.1, C4.1, J1.35, R1.2, R2.2, U1.16 (VCC), U2.16 (VCC), U3.16 (VDD), U4.16 (VDD), U5.16 (VCC)
_OE: J1.41, R2.1, U1.13 (~OE), U2.13 (~OE), U5.13 (~OE)
